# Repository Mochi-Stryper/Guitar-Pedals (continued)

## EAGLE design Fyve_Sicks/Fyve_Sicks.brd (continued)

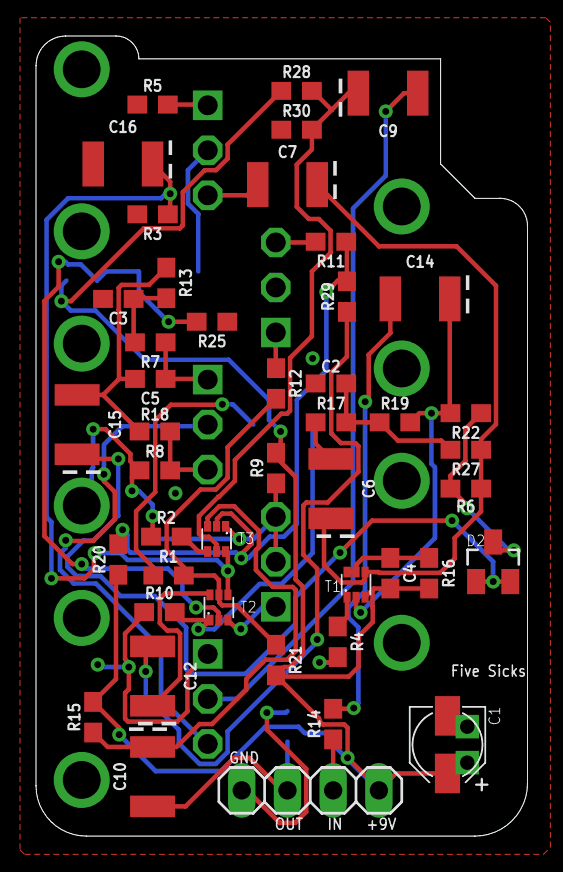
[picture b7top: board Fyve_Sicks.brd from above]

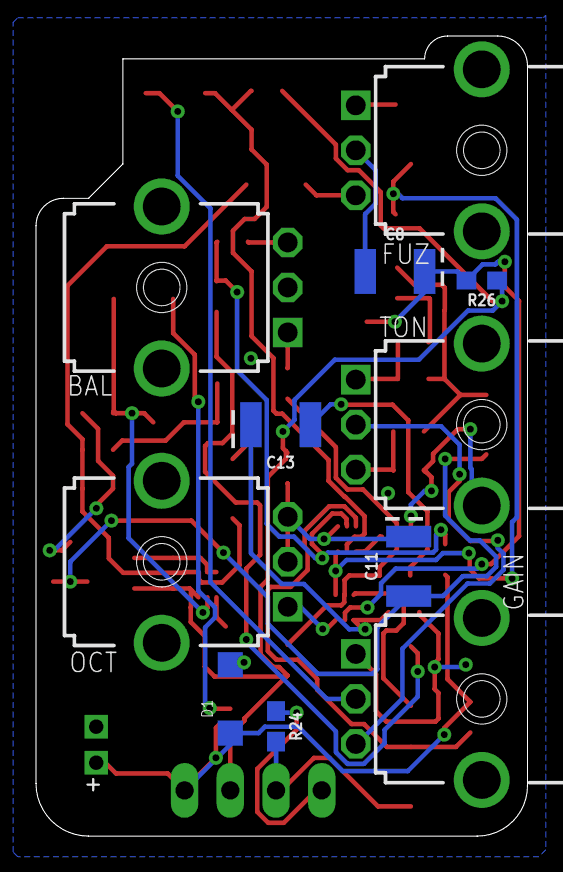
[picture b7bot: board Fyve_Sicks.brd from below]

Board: 2 copper layers, 27.3 x 44.5 mm, 56 parts (11 on the bottom side), 36 nets.
